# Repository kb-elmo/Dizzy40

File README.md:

# Clacky40: 

Yet another replacement Board for the Daisy40. 
Running with a RP2040, adapted from elmos:

--- 
## Status :: 
- PCBs not tested 
- silkscreen missing 
- compatibility with case not validated ( should fit however)

## Features :: 
- RP2040 
- QMK / Vial Support 
- easy to order with Jlcpcb
- supports two encoders 
- additional layout options
- MX Switches 
- additional pinouts for additional LEDS ( 5V+, GND, GPIO)

--- 

## Layouting :: 

## Firmware :: 
pre-compiled file for vial can be found in the **"/firmware"** section.
To enter the bootloader - which is necessary in order to flash a new firmware - press the button next to the encoder on the back of the pcb and plug-it into your keyboard while keeping the button pressed. It should show up as a regular usb-stick in your file explorer now and you can drag the .utf onto this usb-stick. Once done it will restart and use your newly flashed firmware!

## Building your own :: 

On the verge to build this keyboard your own?
Below you can find a little guideline on what is required and how to obtain everything: 

### Getting PCBs ::
in the directory **production** you can find both the gerber and POS-Files required for assembly. 
I usually use JLCPCB for my prototypes, the procedure should be fairly similiar for other manufacturers however, and they require the gerber_buran_pcb.zip and for assembly of all SMD-components also their positions (buran-pos-bottom.csv) and the BOM (buran-BOM.csv) all of which can be found in the **production/assembly** directory. 

---

This work is licensed under a
[Creative Commons Attribution-NonCommercial-ShareAlike 4.0 International License][cc-by-nc-sa].

[![CC BY-NC-SA 4.0][cc-by-nc-sa-image]][cc-by-nc-sa]

[cc-by-nc-sa]: http://creativecommons.org/licenses/by-nc-sa/4.0/
[cc-by-nc-sa-image]: https://licensebuttons.net/l/by-nc-sa/4.0/88x31.png
[cc-by-nc-sa-shield]: https://img.shields.io/badge/License-CC%20BY--NC--SA%204.0-lightgrey.svg

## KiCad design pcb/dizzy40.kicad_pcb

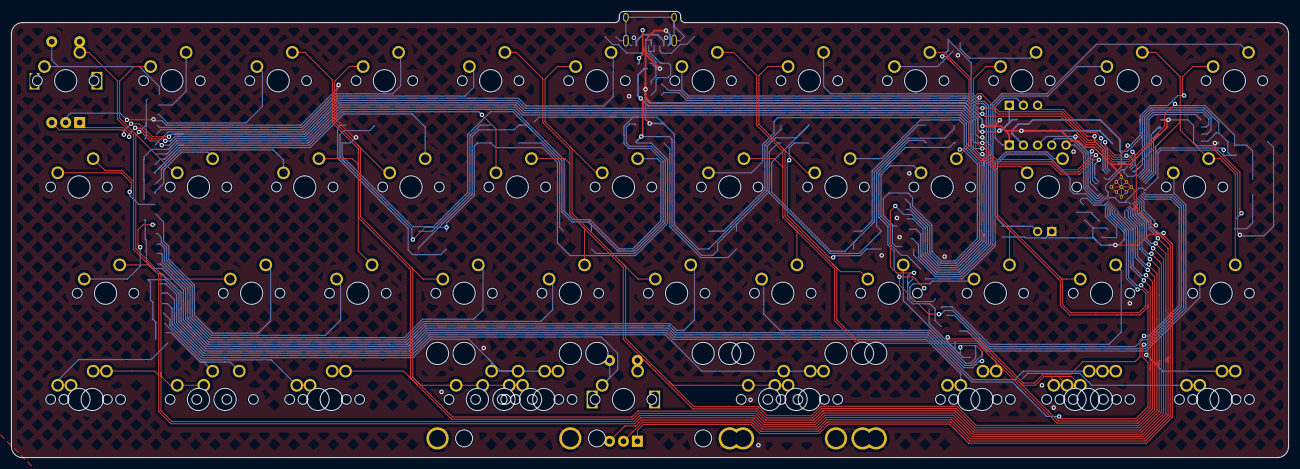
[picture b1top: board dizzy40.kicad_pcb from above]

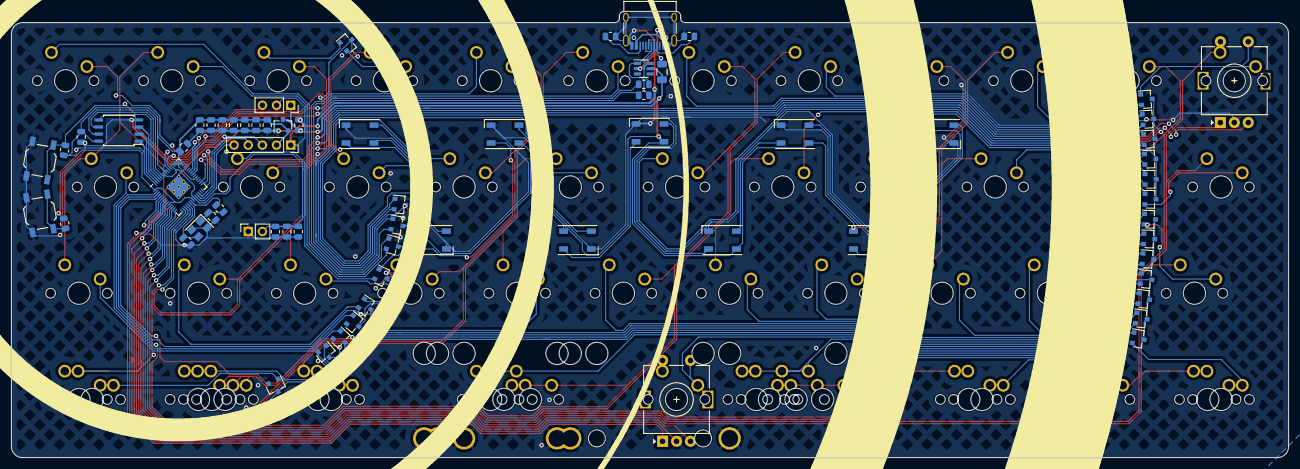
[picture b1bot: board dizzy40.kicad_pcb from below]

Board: 2 copper layers, 229.0 x 80.0 mm, 128 parts (68 on the bottom side), 97 nets.

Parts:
C1, C4, C17: 10u; C_0805_2012Metric
C2, C3: 22pf; C_0805_2012Metric
C5, C6, C7, C9, C11, C12, C13, C14: 100n; C_0805_2012Metric
C8, C10: 1u; C_0805_2012Metric
D17, D18, D19, D20, D21, D22, D23, D24, D25, D26, D27, D28, D29, D30, D31, D32, D33, D34, D35, D36, D37, D38, D39: BAV70; SOT-23
ENC1, ENC2: RotaryEncoder_Switch; RotaryEncoder_Alps_EC11E-Switch_Vertical_H20mm
F0: polyfuse; Fuse_1206_3216Metric
J0: USB_C_Receptacle_USB2.0; USB_C_Receptacle_HRO_TYPE-C-31-M-12
J1: BREAKOUT; PinSocket_1x05_P2.54mm_Vertical
J2: Conn_01x03_Male; PinSocket_1x03_P2.54mm_Vertical
J3, J5, J6, J7, J8: Screw_Terminal_01x02; STAB_MX_P_2u
J4: Breakout 1.1v; PinSocket_1x02_P2.54mm_Vertical
K1, K2, K3, K4, K5, K6, K7, K8, K9, K10, K11, K12, K13, K14, K15, K16, K17, K18, K19, K20, K21, K22, K23, K24, K25, K26, K27, K28, K29, K30, K31, K32, K33, K34, K35, K36, K37, K38, K39, K40, K41, K42, K45, K46, K49, K50, K51, K52, K53, K54, K55, K56, K57, K58, K59: KEYSW; SW_MX_1u
R1, R5: 1k; R_0805_2012Metric
R3, R4: 27; R_0805_2012Metric
R6, R7: 5.1k; R_0805_2012Metric
R8: 10k; R_0805_2012Metric
RGB1, RGB2, RGB3, RGB4, RGB5, RGB6, RGB7, RGB8, RGB9: WS2812B; LED_WS2812B-PLCC4
SW0, SW2: RESET; SW_SPST_TL3342
U2: W25Q128JVS; SOIC-8_5.23x5.23mm_P1.27mm
U3: RP2040; RP2040-QFN-56
U4: XC6206P Smaller footprint, less mA ~.5; SOT-23
U44: SRV05-4; SOT-23-6
Y0: 12MHZ Crystal; Crystal_SMD_3225-4Pin_3.2x2.5mm

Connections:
+1V1: C6.1, C7.1, C8.1, J4.2, U3.23 (DVDD), U3.45 (VREG_VOUT), U3.50 (DVDD)
+3V3: C4.1, C5.1, C9.1, C10.1, C11.1, C12.1, C13.1, C14.1, C17.1, J1.2, R8.2, U2.8 (VCC), U3.1 (IOVDD), U3.10 (IOVDD), U3.22 (IOVDD), U3.33 (IOVDD), U3.42 (IOVDD), U3.43 (ADC_AVDD), U3.44 (VREG_IN), U3.48 (USB_VDD), U3.49 (IOVDD), U4.2 (VO)
+5V: C1.1, F0.2, J2.1, RGB1.1 (VDD), RGB2.1 (VDD), RGB3.1 (VDD), RGB4.1 (VDD), RGB5.1 (VDD), RGB6.1 (VDD), RGB7.1 (VDD), RGB8.1 (VDD), RGB9.1 (VDD), U4.3 (VI), U44.5 (VP)
/MCU/QSPI_SCLK: U2.6 (CLK), U3.52 (QSPI_SCLK)
/MCU/QSPI_SD0: U2.5 (DI(IO0)), U3.53 (QSPI_SD0)
/MCU/QSPI_SD1: U2.2 (DO(IO1)), U3.55 (QSPI_SD1)
/MCU/QSPI_SD2: U2.3 (IO2), U3.54 (QSPI_SD2)
/MCU/QSPI_SD3: U2.7 (IO3), U3.51 (QSPI_SD3)
/MCU/QSPI_SS: R1.1, U2.1 (~CS), U3.56 (QSPI_SS)
/MCU/RUN: J1.3, R8.1, SW2.2, U3.26 (RUN)
/MCU/SWCLK: J1.5, U3.24 (SWCLK)
/MCU/SWD: J1.4, U3.25 (SWD)
/MCU/USB_D+: J0.A6 (D+), J0.B6 (D+), R3.1, U44.1 (IO1)
/MCU/USB_D-: J0.A7 (D-), J0.B7 (D-), R4.1, U44.6 (IO4)
/MCU/XIN: C2.1, U3.20 (XIN), Y0.3
/MCU/XOUT: R5.1, U3.21 (XOUT)
/MCU/~USB_BOOT: R1.2, SW0.2
COL0: ENC1.S2, K1.2, K12.2, K23.2, K34.2, K51.2, U3.8 (GPIO6)
COL1: K2.1, K13.1, K24.1, K35.1, K52.1, U3.9 (GPIO7)
COL2: K3.2, K14.2, K25.2, K36.2, K53.2, U3.11 (GPIO8)
COL3: K4.1, K15.1, K26.1, K37.1, K45.1, K46.1, K54.1, U3.12 (GPIO9)
COL4: ENC2.S2, K5.2, K16.2, K27.2, K38.2, U3.13 (GPIO10)
COL5: K6.1, K17.1, K28.1, K39.1, K55.1, K57.1, U3.14 (GPIO11)
COL6: K7.2, K18.2, K29.2, K40.2, K56.2, U3.15 (GPIO12)
COL7: K8.1, K19.1, K30.1, K41.1, K50.1, K58.1, U3.16 (GPIO13)
COL8: K9.2, K20.2, K31.2, K42.2, K49.2, U3.17 (GPIO14)
COL9: K10.1, K21.1, K32.1, U3.18 (GPIO15)
COL10: K11.2, K22.2, K33.2, U3.5 (GPIO3)
COL11: K59.1, U3.37 (GPIO25)
ENC_ESC_L: ENC1.A, U3.29 (GPIO18)
ENC_ESC_R: ENC1.B, U3.28 (GPIO17)
ENC_ROW_MID: D37.2 (A), ENC2.S1, K38.1
ENC_ROW_TOP: D17.1 (A), ENC1.S1, K1.1
ENC_SPC_L: ENC2.A, U3.6 (GPIO4)
ENC_SPC_R: ENC2.B, U3.7 (GPIO5)
GND: C1.2, C2.2, C3.2, C4.2, C5.2, C6.2, C7.2, C8.2, C9.2, C10.2, C11.2, C12.2, C13.2, C14.2, C17.2, ENC1.C, ENC2.C, J0.A1 (GND), J0.A12 (GND), J0.B1 (GND), J0.B12 (GND), J0.S1 (SHIELD), J1.1, J2.2, J3.1, J3.2, J4.1, J6.1, J7.1, J7.2, J8.1, J8.2, R6.2, R7.2, RGB1.3 (VSS), RGB2.3 (VSS), RGB3.3 (VSS), RGB4.3 (VSS), RGB5.3 (VSS), RGB6.3 (VSS), RGB7.3 (VSS), RGB8.3 (VSS), RGB9.3 (VSS), SW0.1, SW2.1, U2.4 (GND), U3.19 (TESTEN), U3.57 (GND), U4.1 (GND), U44.2 (VN), Y0.2, Y0.4
LED_GLOW: J2.3, U3.36 (GPIO24)
unnamed: C3.1, R5.2, Y0.1
unnamed: D17.2 (A), K2.2
unnamed: D18.1 (A), K3.1
unnamed: D18.2 (A), K4.2
unnamed: D19.1 (A), K5.1
unnamed: D19.2 (A), K6.2
unnamed: D20.1 (A), K7.1
unnamed: D20.2 (A), K8.2
unnamed: D21.1 (A), K10.2
unnamed: D21.2 (A), K9.1
unnamed: D22.1 (A), K59.2
unnamed: D22.2 (A), K11.1
unnamed: D23.1 (A), K13.2
unnamed: D23.2 (A), K12.1
unnamed: D24.1 (A), K15.2
unnamed: D24.2 (A), K14.1
unnamed: D25.1 (A), K17.2
unnamed: D25.2 (A), K16.1
unnamed: D26.1 (A), K19.2
unnamed: D26.2 (A), K18.1
unnamed: D27.1 (A), K20.1
unnamed: D27.2 (A), K21.2
unnamed: D28.1 (A), K22.1
unnamed: D29.1 (A), K24.2
unnamed: D29.2 (A), K23.1
unnamed: D30.1 (A), K25.1
unnamed: D30.2 (A), K26.2
unnamed: D31.1 (A), K27.1
unnamed: D31.2 (A), K28.2
unnamed: D32.1 (A), K30.2
unnamed: D32.2 (A), K29.1
unnamed: D33.1 (A), K31.1
unnamed: D33.2 (A), K32.2
unnamed: D34.1 (A), K33.1
unnamed: D35.1 (A), K35.2, K52.2
unnamed: D35.2 (A), K34.1, K51.1
unnamed: D36.1 (A), K37.2, K45.2, K46.2, K54.2
unnamed: D36.2 (A), K36.1, K53.1
unnamed: D37.1 (A), K39.2, K55.2, K57.2
unnamed: D38.1 (A), K41.2, K50.2, K58.2
unnamed: D38.2 (A), K40.1, K56.1
unnamed: D39.1 (A), K42.1, K49.1
unnamed: J0.A5 (CC1), R7.1
unnamed: J0.B5 (CC2), R6.1
unnamed: RGB1.2 (DOUT), RGB2.4 (DIN)
unnamed: RGB2.2 (DOUT), RGB3.4 (DIN)
unnamed: RGB3.2 (DOUT), RGB4.4 (DIN)
unnamed: RGB4.2 (DOUT), RGB5.4 (DIN)
unnamed: RGB5.2 (DOUT), RGB6.4 (DIN)
unnamed: RGB6.2 (DOUT), RGB7.4 (DIN)
unnamed: RGB7.2 (DOUT), RGB8.4 (DIN)
unnamed: RGB8.2 (DOUT), RGB9.4 (DIN)
unnamed: R4.2, U3.46 (USB_DM)
unnamed: R3.2, U3.47 (USB_DP)
RGB: RGB1.4 (DIN), U3.3 (GPIO1)
ROW0: D17.3 (K), D18.3 (K), D19.3 (K), D20.3 (K), D21.3 (K), D22.3 (K), U3.30 (GPIO19)
ROW1: D23.3 (K), D24.3 (K), D25.3 (K), D26.3 (K), D27.3 (K), D28.3 (K), U3.35 (GPIO23)
ROW2: D29.3 (K), D30.3 (K), D31.3 (K), D32.3 (K), D33.3 (K), D34.3 (K), U3.4 (GPIO2)
ROW3: D35.3 (K), D36.3 (K), D37.3 (K), D38.3 (K), D39.3 (K), U3.2 (GPIO0)
VBUS: F0.1, J0.A4 (VBUS), J0.A9 (VBUS), J0.B4 (VBUS), J0.B9 (VBUS)

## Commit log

2022-06-06 add teardrops
2022-06-06 cleanup traces
2022-06-07 finalize fab version
2022-06-07 update LED part number
2022-07-07 add custom plate
2023-05-04 outline for updated project
2023-05-21 diode positioning done
2023-05-22 positions reset buttons, routing
2023-05-31 finalized routing, placement of components
